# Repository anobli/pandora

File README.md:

# Pandora

Open Hardware and Open Source Home Automation Platform

## Overview

**Pandora** is an open platform for building robust home automation devices that gives users complete control over their smart home ecosystem. Built on the Zephyr RTOS and leveraging modern IoT protocols like WiFi and Thread/OpenThread with CoAP, Pandora addresses the key issues with current smart home devices: privacy concerns, cloud dependency, vendor lock-in, and planned obsolescence.

### Key Principles

- **User-repairable hardware** - Open hardware designs that users can modify and repair
- **Local processing** - No cloud dependency, all processing happens locally  
- **Open source software stack** - Complete control over firmware and functionality
- **Give back control to users** - No vendor lock-in or forced obsolescence

### Hermes Subsystem

The **Hermes subsystem** is the core IoT framework that provides:

- **Automatic Discovery**: Devices automatically discover and register with servers
- **State Management**: Comprehensive device lifecycle and state machine
- **CoAP Communication**: Both client and server functionality
- **Network Management**: Automatic connection and device provisioning
- **Persistent Settings**: Configuration survives device reboots
- **Extensible Architecture**: Easy to add new device types

## Current Status

### Working Features
- Power/Light switch devices running on Zephyr
- CoAP-based device discovery and control
- JSON API for device state management
- Multiple development platform support
- **WiFi connectivity**: ESP32/ESP32C6 with automatic provisioning
- **Thread networking**: CC1352P7 with OpenThread support
- Persistent configuration storage

### In Development
- MCUboot integration for secure OTA updates
- Enhanced security and encryption
- Matter protocol migration
- More device type support

## Quick Start

### Prerequisites
- Zephyr SDK and development environment
- Supported development board (ESP32 DevKit or CC1352P7-LP recommended)
- West tool for project management

### Building a Sample Application

```bash
# Clone the repository
git clone https://github.com/anobli/pandora.git
cd pandora

# Initialize west workspace
west init -l .
west update

# Build for WiFi-based device (ESP32)
west build -b esp32_devkitc_procpu samples/hermes/hermes_light

# Or build for Thread-based device (CC1352P7)
west build -b cc1352p7_lp samples/hermes/hermes_light

# Flash to device
west flash
```

## Device Types

### Currently Supported
- **Light Controllers**: On/off, dimming, color temperature, RGB control
- **Power Switches**: Relay-based switching modules

### Planned
- Light bulbs with integrated controllers
- Door/window sensors
- Motion detectors
- Climate sensors

## Integration

### CoAP2MQTT Bridge
For integration with MQTT-based home automation systems, use the companion [CoAP2MQTT](https://github.com/anobli/coap2mqtt) bridge.

#### Home Assistant Integration
Pandora devices integrate with Home Assistant through the CoAP2MQTT bridge:
- **CoAP to MQTT translation**: Bridge handles protocol conversion
- **Automatic device discovery** in Home Assistant via MQTT discovery
- **Standard entity types** (lights, switches, sensors)
- **Real-time state updates** with immediate response
- **Network flexibility**: Works with both WiFi and Thread networks

## Development

### Adding New Device Types

1. Create device tree bindings in `dts/bindings/`
2. Implement driver in `drivers/` if needed
3. Add device-specific service in `subsys/hermes/`
4. Create sample application in `samples/`

### Contributing

Contributions are welcome! Please see:
- **Hardware designs**: https://github.com/anobli/pandora-hw
- **CoAP2MQTT bridge**: https://github.com/anobli/coap2mqtt
- **Main firmware**: This repository

## License

This project is licensed under the Apache 2.0 License - see the individual file headers for details.

## Future Plans

- **Matter Support**: Migration from custom CoAP to Matter protocol
- **Enhanced Security**: Full encryption and secure provisioning
- **Consumer Products**: Moving beyond maker-friendly to consumer-ready devices
- **Extended Device Support**: More sensors, actuators, and device types
- **Cloud Integration**: Optional cloud services while maintaining local control

---

*Pandora: Giving users back control of their smart homes*

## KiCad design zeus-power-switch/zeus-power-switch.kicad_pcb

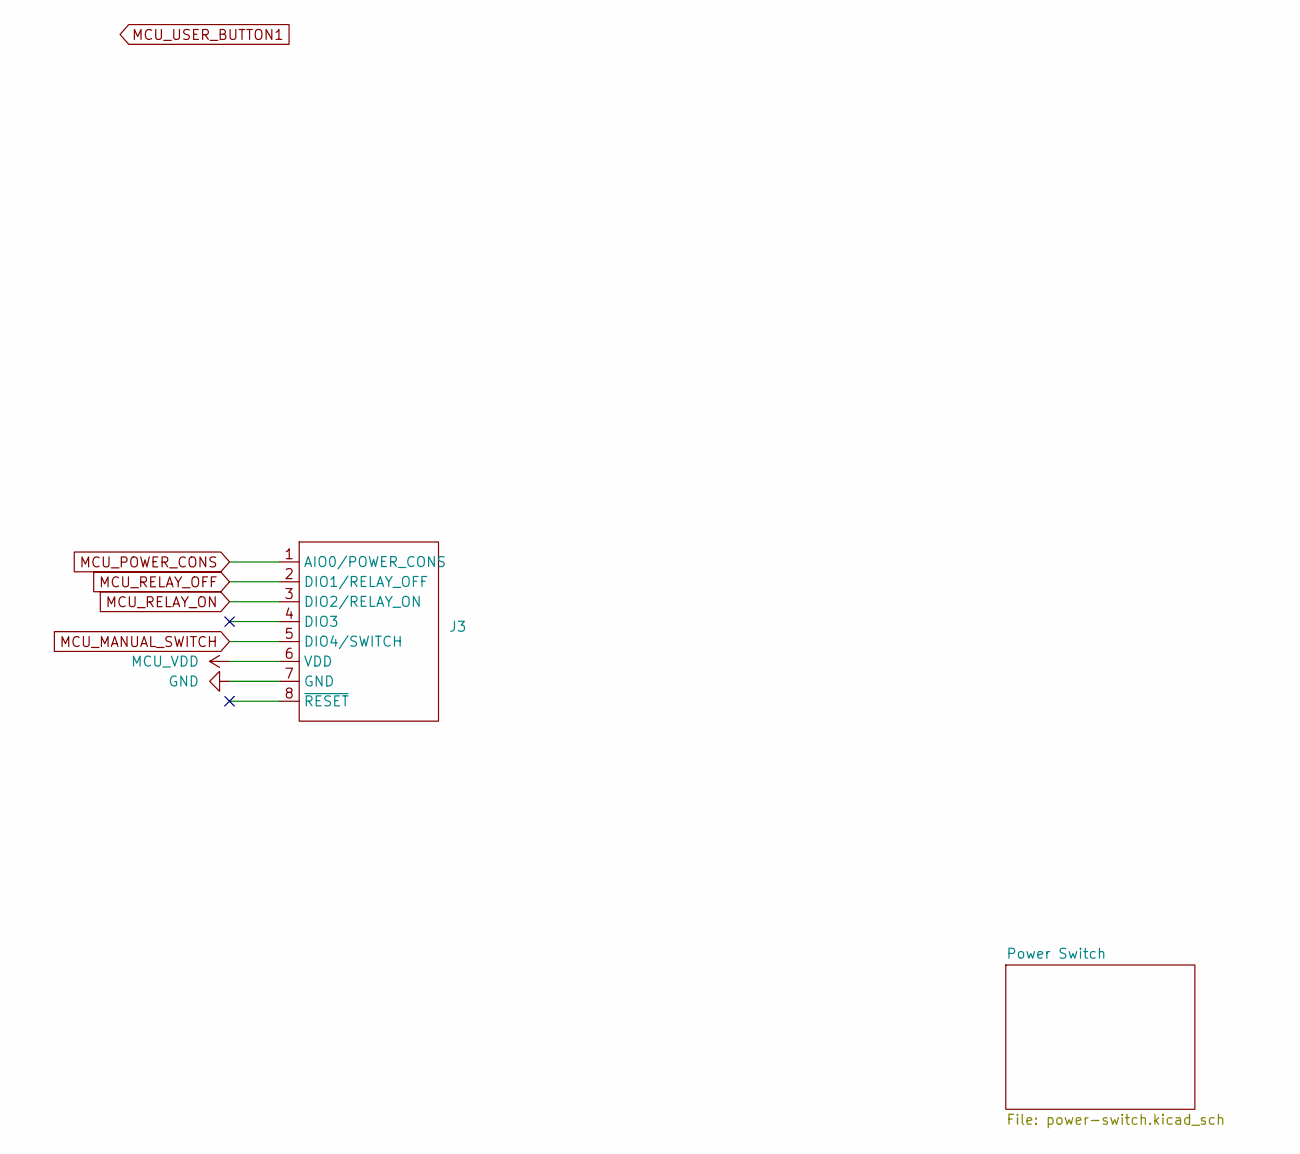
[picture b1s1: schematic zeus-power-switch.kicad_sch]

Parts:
J3: Zeus Connector_1

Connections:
GND: J3.7 (GND); also elsewhere on the board
MCU_MANUAL_SWITCH: J3.5 (DIO4/SWITCH); also elsewhere on the board
MCU_POWER_CONS: J3.1 (AIO0/POWER_CONS); also elsewhere on the board
MCU_RELAY_OFF: J3.2 (DIO1/RELAY_OFF); also elsewhere on the board
MCU_RELAY_ON: J3.3 (DIO2/RELAY_ON); also elsewhere on the board
MCU_VDD: J3.6 (VDD); also elsewhere on the board

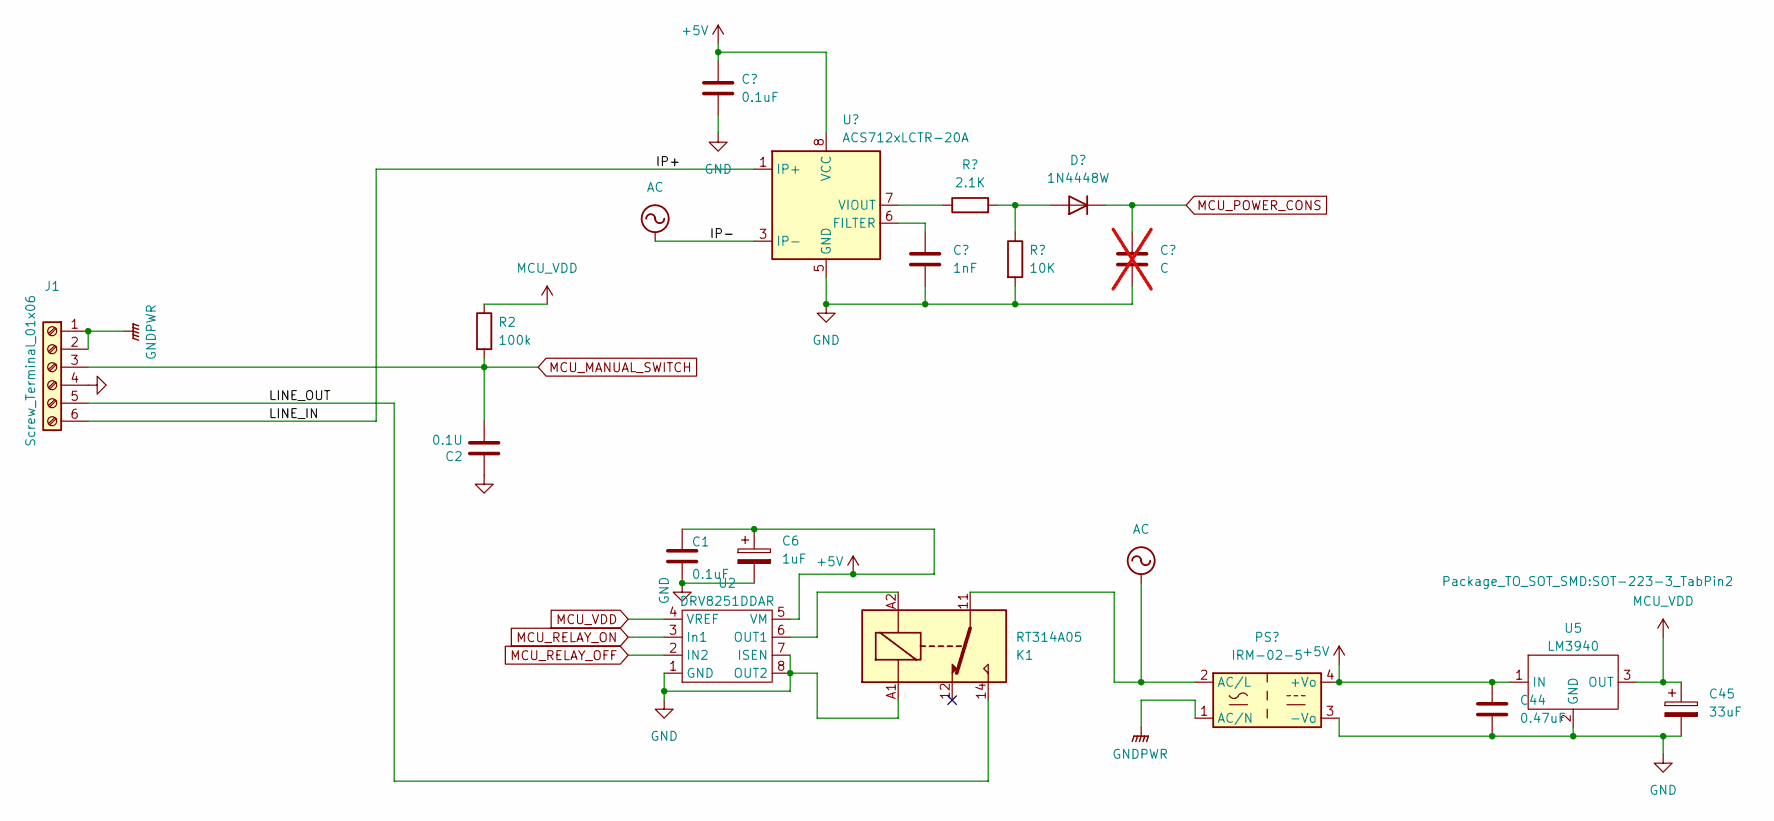
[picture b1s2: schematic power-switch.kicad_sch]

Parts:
C1, C3: 0.1uF; C_0402_1005Metric; MPN1 GRM155C81E104MA12D
C2: 0.1U; C_0402_1005Metric; MPN1 CL05A104MP5NNNC
C4: 1nF; C_0402_1005Metric; MPN1 VJ0402Y102MXBAC
C5: C; C_0402_1005Metric; not fitted
C6: 1uF; C_0402_1005Metric; MPN1 GRT153R61A105ME13D
C44: 0.47uF; C_0402_1005Metric; MPN1 GRM155R71A474KE01D
C45: 33uF; C_1206_3216Metric; MPN1 C3216X5R1E336M160AC
D3: 1N4448W; D_SOD-123; MPN1 1N4448W-7-F
J1: Screw_Terminal_01x06; TE-2-796683-8; MPN1 796683-6
K1: RT314A05; Relay_SPDT_Schrack-RT1-16A-FormC_RM5mm; MPN1 RT314A05
PS1: IRM-02-5; Converter_ACDC_MeanWell_IRM-02-xx_THT; MPN1 IRM-02-5
R2: 100k; R_0402_1005Metric; MPN1 CRCW0402100KFKED
R5: 2.1K; R_0402_1005Metric; MPN1 CRCW04022K10FKED
R7: 10K; R_0402_1005Metric; MPN1 CRCW040210K0FKEDC
U1: ACS712xLCTR-20A; SOIC-8_3.9x4.9mm_P1.27mm; MPN1 ACS712ELCTR-20A-T
U2: DRV8251DDAR; Texas_HSOP-8-1EP_3.9x4.9mm_P1.27mm_ThermalVias; MPN1 DRV8251DDAR
U5: LM3940; SOT-223-3_TabPin2; MPN1 LM3940IMP-3.3/NOPB

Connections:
+5V: C1.1, C3.1, C6.1, C44.1, PS1.4 (+Vo), U1.8 (VCC), U2.5 (VM), U5.1 (IN)
/Power Switch/IP+: J1.6, U1.1 (IP+), U1.2 (IP+)
/Power Switch/LINE_OUT: J1.5, K1.14
AC: K1.11, PS1.2 (AC/L), U1.3 (IP-), U1.4 (IP-)
GND: C1.2, C2.2, C3.2, C4.2, C5.2, C6.2, C44.2, C45.2, J1.4, K1.A1, PS1.3 (-Vo), R7.2, U1.5 (GND), U2.1 (GND), U2.7 (ISEN), U2.8 (OUT2), U5.2 (GND); also elsewhere on the board
GNDPWR: J1.1, J1.2, PS1.1 (AC/N)
MCU_MANUAL_SWITCH: C2.1, J1.3, R2.2; also elsewhere on the board
MCU_POWER_CONS: C5.1, D3.1 (K); also elsewhere on the board
MCU_RELAY_OFF: U2.2 (IN2); also elsewhere on the board
MCU_RELAY_ON: U2.3 (In1); also elsewhere on the board
MCU_VDD: C45.1, R2.1, U2.4 (VREF), U5.3 (OUT); also elsewhere on the board
unnamed: D3.2 (A), R5.2, R7.1
unnamed: C4.1, U1.6 (FILTER)
unnamed: R5.1, U1.7 (VIOUT)
unnamed: K1.A2, U2.6 (OUT1)

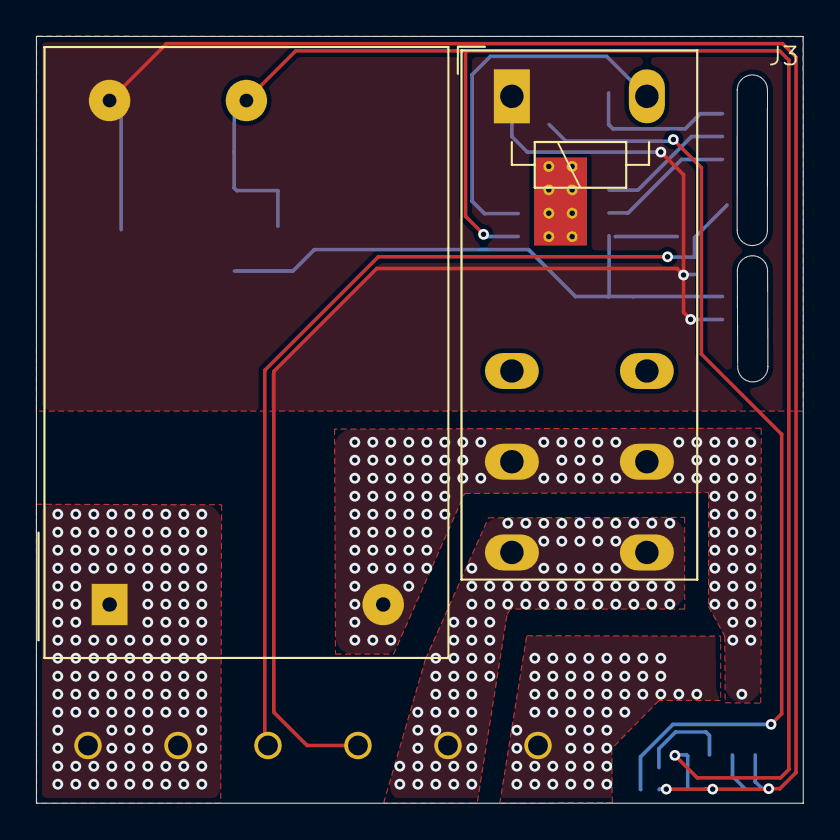
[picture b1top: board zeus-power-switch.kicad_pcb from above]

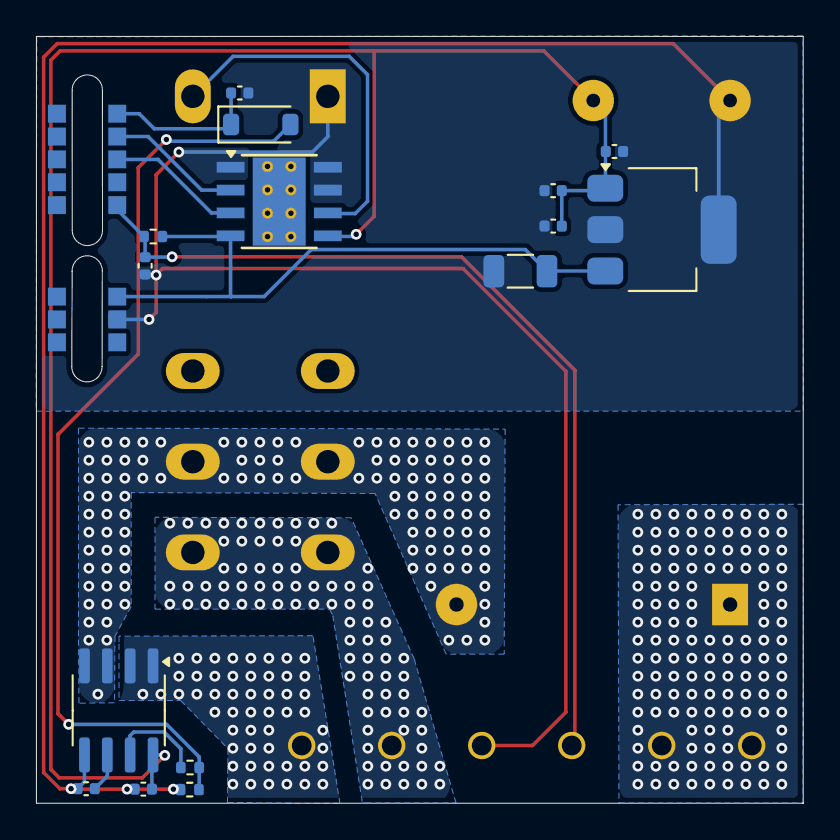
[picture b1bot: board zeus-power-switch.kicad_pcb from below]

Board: 2 copper layers, 42.6 x 42.6 mm, 19 parts (15 on the bottom side), 15 nets.

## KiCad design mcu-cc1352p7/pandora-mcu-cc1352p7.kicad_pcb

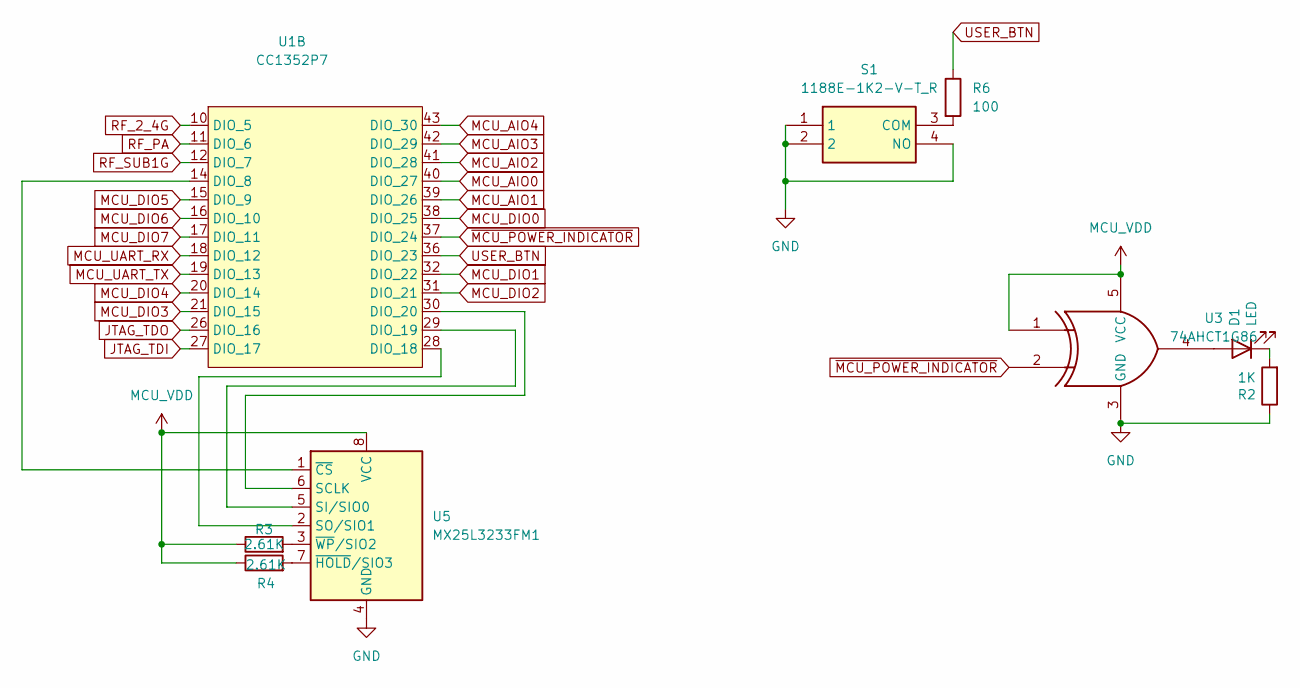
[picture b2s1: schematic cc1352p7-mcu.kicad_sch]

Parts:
D1: LED; LED_0402_1005Metric; MPN1 LT QH9G-Q2OO-25-2Z4Y-5-R18
R2: 1K; R_0402_1005Metric; MPN1 RC0402JR-071KL
R3, R4: 2.61K; R_0201_0603Metric
R6: 100; R_0402_1005Metric
S1: 1188E-1K2-V-T_R; 1188E1K2VTR; Mouser Part Number 113-1188E1K2VTR
U1: CC1352P7; Texas_RGZ0048A_VQFN-48-1EP_7x7mm_P0.5mm_EP5.15x5.15mm_Therm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; MPN1 CC1352P74T0RGZR
U3: 74AHCT1G86; SOT-23-5; MPN1 SN74AHCT1G86DBVT
U5: MX25L3233FM1; SOP-8_3.9x4.9mm_P1.27mm; MPN1 MX25L3233FM1I-08G

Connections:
GND: R2.1, S1.1, S1.2, S1.4 (NO), U3.3 (GND), U5.4 (GND); also elsewhere on the board
JTAG_TDI: U1.27 (DIO_17); also elsewhere on the board
JTAG_TDO: U1.26 (DIO_16); also elsewhere on the board
MCU_AIO0: U1.40 (DIO_27); also elsewhere on the board
MCU_AIO1: U1.39 (DIO_26); also elsewhere on the board
MCU_AIO2: U1.41 (DIO_28); also elsewhere on the board
MCU_AIO3: U1.42 (DIO_29); also elsewhere on the board
MCU_AIO4: U1.43 (DIO_30); also elsewhere on the board
MCU_DIO0: U1.38 (DIO_25); also elsewhere on the board
MCU_DIO1: U1.32 (DIO_22); also elsewhere on the board
MCU_DIO2: U1.31 (DIO_21); also elsewhere on the board
MCU_DIO3: U1.21 (DIO_15); also elsewhere on the board
MCU_DIO4: U1.20 (DIO_14); also elsewhere on the board
MCU_DIO5: U1.15 (DIO_9); also elsewhere on the board
MCU_DIO6: U1.16 (DIO_10); also elsewhere on the board
MCU_DIO7: U1.17 (DIO_11); also elsewhere on the board
MCU_UART_RX: U1.18 (DIO_12); also elsewhere on the board
MCU_UART_TX: U1.19 (DIO_13); also elsewhere on the board
MCU_VDD: R3.1, R4.1, U3.1, U3.5 (VCC), U5.8 (VCC); also elsewhere on the board
unnamed: D1.2 (A), U3.4
unnamed: D1.1 (K), R2.2
unnamed: R6.2, S1.3 (COM)
unnamed: U1.14 (DIO_8), U5.1 (~CS)
unnamed: U1.28 (DIO_18), U5.2 (SO/SIO1)
unnamed: U1.29 (DIO_19), U5.5 (SI/SIO0)
unnamed: U1.30 (DIO_20), U5.6 (SCLK)
unnamed: R4.2, U5.7 (~HOLD/SIO3)
unnamed: R3.2, U5.3 (~WP/SIO2)
RF_2_4G: U1.10 (DIO_5); also elsewhere on the board
RF_PA: U1.11 (DIO_6); also elsewhere on the board
RF_SUB1G: U1.12 (DIO_7); also elsewhere on the board
USER_BTN: R6.1, U1.36 (DIO_23)
~MCU_POWER_INDICATOR: U1.37 (DIO_24), U3.2

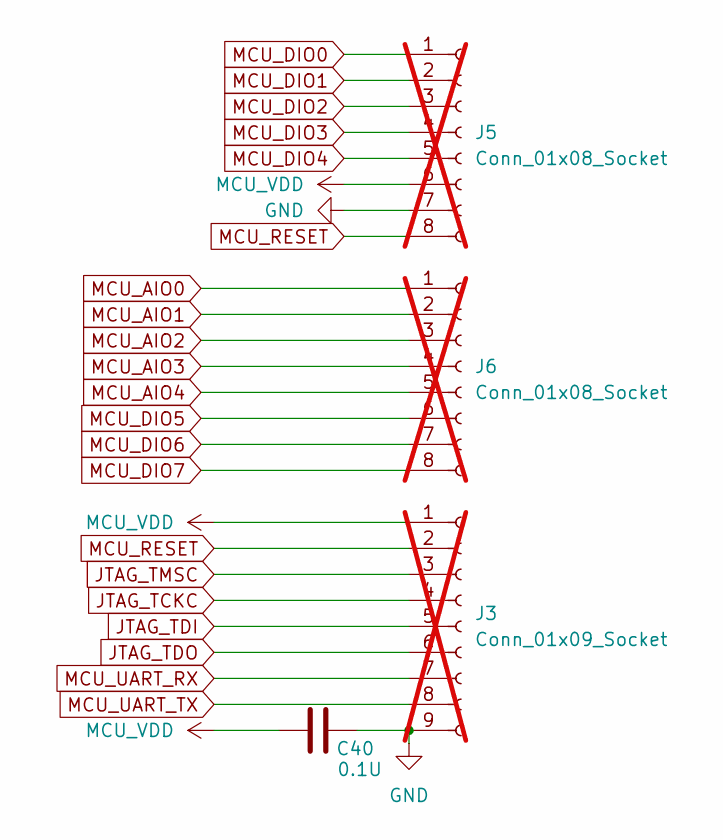
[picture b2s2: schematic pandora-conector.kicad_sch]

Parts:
C40: 0.1U; C_0402_1005Metric; MPN1 CL05A104MP5NNNC
J3: Conn_01x09_Socket; Pandora Connector 9; not fitted
J5: Conn_01x08_Socket; Zeus Connector; not fitted
J6: Conn_01x08_Socket; Pandora Connector 8; not fitted

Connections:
GND: C40.2, J3.9, J5.7; also elsewhere on the board
JTAG_TCKC: J3.4; also elsewhere on the board
JTAG_TDI: J3.5; also elsewhere on the board
JTAG_TDO: J3.6; also elsewhere on the board
JTAG_TMSC: J3.3; also elsewhere on the board
MCU_AIO0: J6.1; also elsewhere on the board
MCU_AIO1: J6.2; also elsewhere on the board
MCU_AIO2: J6.3; also elsewhere on the board
MCU_AIO3: J6.4; also elsewhere on the board
MCU_AIO4: J6.5; also elsewhere on the board
MCU_DIO0: J5.1; also elsewhere on the board
MCU_DIO1: J5.2; also elsewhere on the board
MCU_DIO2: J5.3; also elsewhere on the board
MCU_DIO3: J5.4; also elsewhere on the board
MCU_DIO4: J5.5; also elsewhere on the board
MCU_DIO5: J6.6; also elsewhere on the board
MCU_DIO6: J6.7; also elsewhere on the board
MCU_DIO7: J6.8; also elsewhere on the board
MCU_RESET: J3.2, J5.8; also elsewhere on the board
MCU_UART_RX: J3.7; also elsewhere on the board
MCU_UART_TX: J3.8; also elsewhere on the board
MCU_VDD: C40.1, J3.1, J5.6; also elsewhere on the board

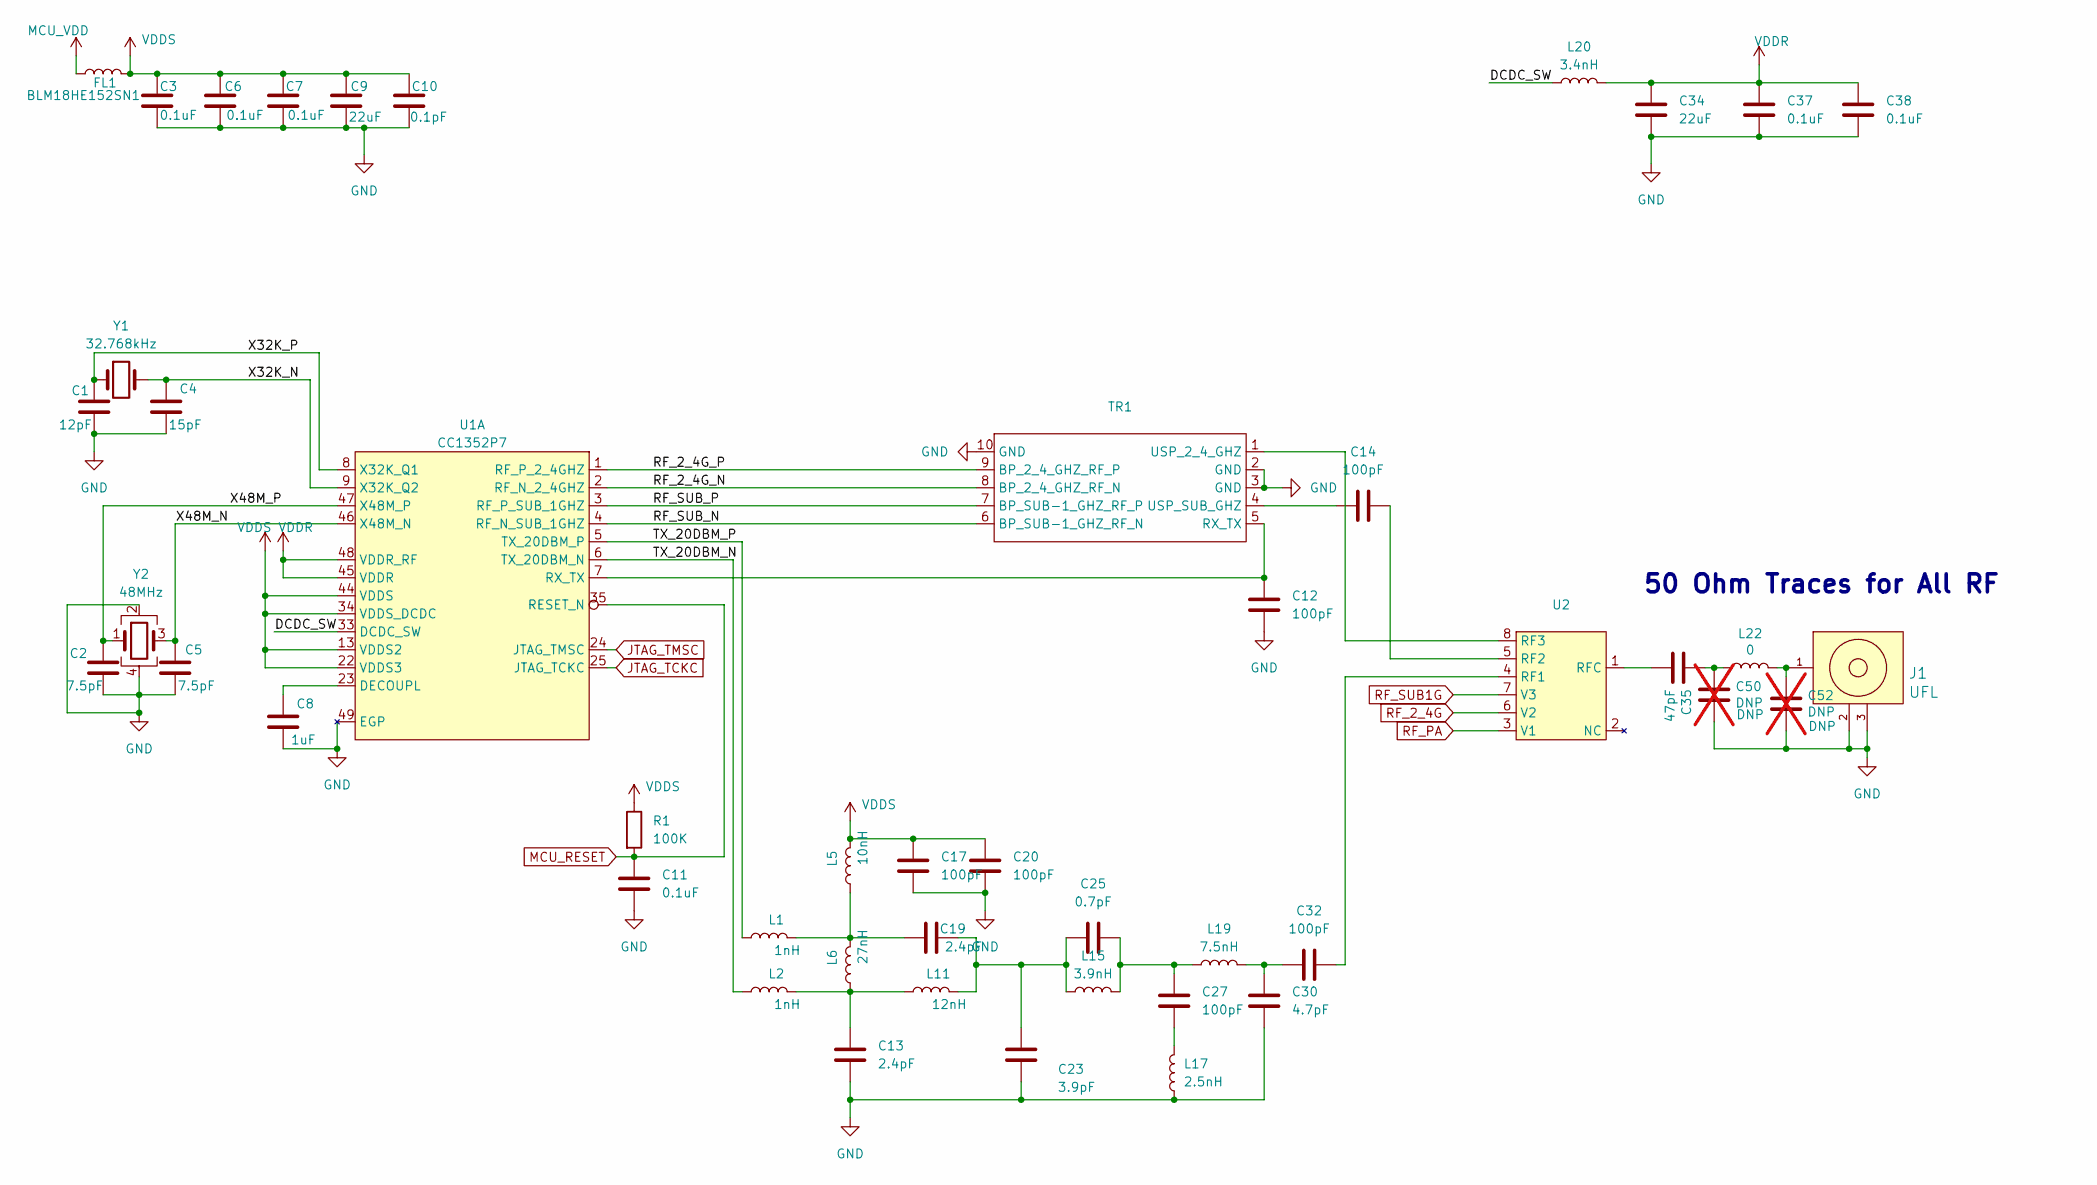
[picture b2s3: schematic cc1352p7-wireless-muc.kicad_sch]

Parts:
C1: 12pF; C_0201_0603Metric; MPN1 GJM1555C1H120JB01D
C2, C5: 7.5pF; C_0201_0603Metric; MPN1 GRM0335C1H7R5BA01J
C3, C6, C7, C11, C37, C38: 0.1uF; C_0402_1005Metric; MPN1 GRM155R71E104KE14D
C4: 15pF; C_0201_0603Metric; MPN1 GRT1555C1H150JA02D
C8: 1uF; C_0402_1005Metric; MPN1 GRM155C81C105KE15D
C9, C34: 22uF; C_0603_1608Metric; MPN1 GRM188R60J226MEA0D
C10: 0.1pF; C_0201_0603Metric; MPN1 GRM155R71E104KE14D
C12, C14: 100pF; C_0201_0603Metric
C13, C19: 2.4pF; C_0201_0603Metric; MPN1 GRM0335C1H2R4BA01J
C17, C20, C27, C32: 100pF; C_0201_0603Metric; MPN1 GRM0335C1H101GA01D
C23: 3.9pF; C_0201_0603Metric; MPN1 GRM0335C1H3R9BA01J
C25: 0.7pF; C_0201_0603Metric; MPN1 GRM0335C1HR70WA01D
C30: 4.7pF; C_0201_0603Metric; MPN1 GRM0335C1H4R7BA01J
C35: 47pF; C_0201_0603Metric; MPN1 GRM0335C1E470JA01D
C50: DNP; C_0201_0603Metric; MPN1 CC0402CRNPO9BN2R7; not fitted
C52: DNP; C_0201_0603Metric; MPN1 CC0402DRNPO9BN5R6; not fitted
FL1: BLM18HE152SN1; L_0603_1608Metric
J1: UFL; A-1JB; MPN1 A-1JB
L1, L2: 1nH; L_0201_0603Metric; MPN1 LQP03TN3N7B02J
L5: 10nH; L_0201_0603Metric; MPN1 LQP03TN12NHZ2J
L6: 27nH; L_0201_0603Metric; MPN1 LQP03TN27NHZ2J
L11: 12nH; L_0201_0603Metric; MPN1 LQP03TN12NHZ2J
L15: 3.9nH; L_0201_0603Metric; MPN1 LQP03TN3N9B02J
L17: 2.5nH; L_0201_0603Metric; MPN1 LQP03TN2N5B02J
L19: 7.5nH; L_0201_0603Metric; MPN1 LQP03TN7N5HZ2J
L20: 3.4nH; L_0201_0603Metric; MPN1 LQP03TN3N4B02J
L22: 0; L_0201_0603Metric; MPN1 RMCF0402ZT0R00
R1: 100K; R_0402_1005Metric; MPN1 CRCW0402100KJNED
TR1: IPC1352; MPN1 LFB21868MDZ5E757
U1: CC1352P7; Texas_RGZ0048A_VQFN-48-1EP_7x7mm_P0.5mm_EP5.15x5.15mm_Therm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; MPN1 CC1352P74T0RGZR
U2: Skyworks_SKY1337-373LF; MPN1 SKY13317-373LF
Y1: 32.768kHz; Crystal_SMD_2012-2Pin_2.0x1.2mm; MPN1 830050789
Y2: 48MHz; Crystal_SMD_2016-4Pin_2.0x1.6mm; MPN1 ASDAIG-48.000MHZ-X-K-T

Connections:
/CC1352P7-Wireless-MCU/DCDC_SW: L20.1, U1.33 (DCDC_SW)
/CC1352P7-Wireless-MCU/RF_2_4G_N: TR1.8 (BP_2_4_GHZ_RF_N), U1.2 (RF_N_2_4GHZ)
/CC1352P7-Wireless-MCU/RF_2_4G_P: TR1.9 (BP_2_4_GHZ_RF_P), U1.1 (RF_P_2_4GHZ)
/CC1352P7-Wireless-MCU/RF_SUB_N: TR1.6 (BP_SUB-1_GHZ_RF_N), U1.4 (RF_N_SUB_1GHZ)
/CC1352P7-Wireless-MCU/RF_SUB_P: TR1.7 (BP_SUB-1_GHZ_RF_P), U1.3 (RF_P_SUB_1GHZ)
/CC1352P7-Wireless-MCU/TX_20DBM_N: L2.1, U1.6 (TX_20DBM_N)
/CC1352P7-Wireless-MCU/TX_20DBM_P: L1.1, U1.5 (TX_20DBM_P)
/CC1352P7-Wireless-MCU/X32K_N: C4.1, U1.9 (X32K_Q2), Y1.2
/CC1352P7-Wireless-MCU/X32K_P: C1.1, U1.8 (X32K_Q1), Y1.1
/CC1352P7-Wireless-MCU/X48M_N: C5.1, U1.46 (X48M_N), Y2.3
/CC1352P7-Wireless-MCU/X48M_P: C2.1, U1.47 (X48M_P), Y2.1
GND: C1.2, C2.2, C3.2, C4.2, C5.2, C6.2, C7.2, C8.2, C9.2, C10.2, C11.2, C12.1, C13.1, C17.1, C20.1, C23.1, C30.1, C34.2, C37.2, C38.2, C50.2, C52.2, J1.2, J1.3, L17.1, TR1.2 (GND), TR1.3 (GND), TR1.10 (GND), U1.49 (EGP), Y2.2, Y2.4; also elsewhere on the board
JTAG_TCKC: U1.25 (JTAG_TCKC); also elsewhere on the board
JTAG_TMSC: U1.24 (JTAG_TMSC); also elsewhere on the board
MCU_RESET: C11.1, R1.2, U1.35 (RESET_N); also elsewhere on the board
MCU_VDD: FL1.1; also elsewhere on the board
unnamed: C13.2, L2.2, L6.1, L11.1
unnamed: C19.1, L1.2, L5.1, L6.2
unnamed: C19.2, C23.2, C25.2, L11.2, L15.1
unnamed: C25.1, C27.2, L15.2, L19.1
unnamed: C27.1, L17.2
unnamed: C30.2, C32.1, L19.2
unnamed: C35.2, C50.1, L22.2
unnamed: C52.1, J1.1, L22.1
unnamed: C12.2, TR1.5 (RX_TX), U1.7 (RX_TX)
unnamed: TR1.1 (USP_2_4_GHZ), U2.8 (RF3)
unnamed: C14.1, TR1.4 (USP_SUB_GHZ)
unnamed: C8.1, U1.23 (DECOUPL)
unnamed: C32.2, U2.4 (RF1)
unnamed: C14.2, U2.5 (RF2)
unnamed: C35.1, U2.1 (RFC)
RF_2_4G: U2.6 (V2); also elsewhere on the board
RF_PA: U2.3 (V1); also elsewhere on the board
RF_SUB1G: U2.7 (V3); also elsewhere on the board
VDDR: C34.1, C37.1, C38.1, L20.2, U1.45 (VDDR), U1.48 (VDDR_RF)
VDDS: C3.1, C6.1, C7.1, C9.1, C10.1, C17.2, C20.2, FL1.2, L5.2, R1.1, U1.13 (VDDS2), U1.22 (VDDS3), U1.34 (VDDS_DCDC), U1.44 (VDDS)

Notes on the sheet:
50 Ohm Traces for All RF

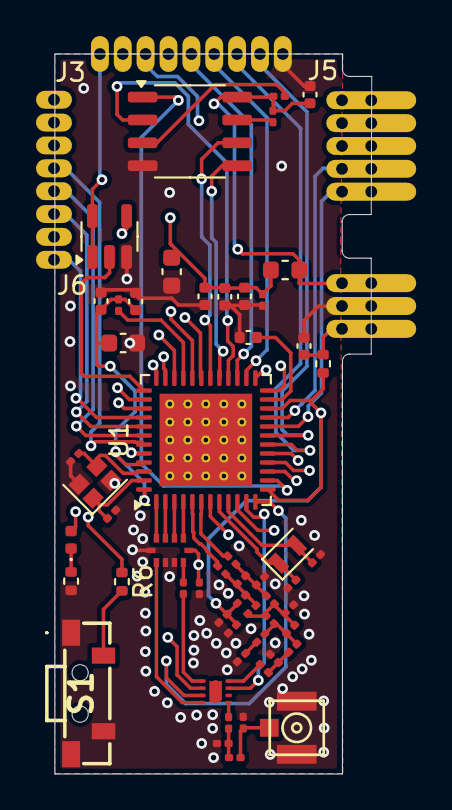
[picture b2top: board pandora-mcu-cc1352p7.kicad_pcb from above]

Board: 4 copper layers, 17.6 x 40.0 mm, 58 parts (0 on the bottom side), 64 nets.

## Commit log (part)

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2025-02-25 Create Pandora project
    Pandora projects intends to develop open source and open hardware
    solutions for the home automation.
    This adds the kicad projects for Zeus board (a connected power switch)
    and the MCU board. This is the DVT0 version.
2025-06-11 Initial commit
    Create a new tree for Pandora project.
    Pandora intends to provides open sources firmware for home automation
    devices. It first intends to support open hardware devices but it will
    also support ESP32 based devices.
    This will provides BSP, samples for demonstrating some connectivity
    features and full applications.
2025-06-13 Add .clang-format from Zephyr
    In order to use clang-format, add .clang-format.
    Because most of the code here is intended to be upstreamed to Zephyr,
    use the same config.
2025-06-13 drivers: sensor: Add support of sensor simulator
    This adds a simulator for sensor.
    This could be used for unit tests or for development when
    using the sensor API with native sim.
2025-06-13 samples: Add a sample demonstrating how using the sensor simulator
    This adds a basic example show how to use the sensor simulator.
    This shows how we could set default value and noise programmatically.
    An alternative way of doing it is using DTS which allow using the
    simulator with regular sample applications using the sensor API.
2025-07-31 WIP: First working light sample
2025-07-31 add narada light sample
2025-07-31 WIP: Add a light sample using narada
2025-07-31 minor fix to narada
2025-08-04 add support of rgbct light
2025-08-23 pandora: Add support of syscall
    We are going to define new driver APIs.
    This adds anything required to do it.
2025-08-23 subsys: Add support of hermes
    This adds hermes, a library that implements communication
    between home automation devices.
2025-08-23 hermes: Add support of settings
    This adds support of settings.
    This allows saving and restoring entity state after a power cycle.
    We may also want to save some user settings later such as schedules
    if status LED should be enabled or not, and so on.
2025-08-23 Add a README
    This adds a README file to explain what is Pandora.
2025-08-23 hermes: Add a shell for hermes
    This adds a development shell for hermes.
    This is useful as example to reset device configuration.
2025-08-24 Add license file and update sources with SPDX license
    Currently, the license is not clearly defined.
    This makes sure that everything is clearly defined.
2025-08-26 drivers: light: Add support of light GPIO driver
    This adds support of a GPIO light driver.
2025-08-28 hermes: Add support of native_sim target
    This adds some changes required to use native_sim
    for developping and testing hermes.
2025-10-28 Add support of ESPHOME
    This add a preliminary support of ESPHOME to zephyr.
    This currently supports the following components:
    - api
    - hbridge and gpio switch
    - button
    - gpio binary sensor
2025-10-28 net: esphome: esphome: Fix the loop delay
    The on_loop method is expected to be run every 16ms.
    This updates the delay to respect it.
2025-10-28 esphome: switch: hbridge: Fix a build issue in the hbridge component
    This addresses a build issue in the hbridge switch component.
2025-10-28 net: esphome: logger: Add missing Kconfig symbol
    CMake is expecting a Kconfig symbol to build the logger
    but this symbols is never defined.
    This defines a kconfig symbol and use it in CMake.
2025-10-28 ESPHome app: Add a config overlay to enable support of OpenThread
    This adds an overlay to enable support of OpenThread network.
    The overlay use predefined newtork settings which allow testing
    quickly a device using OpenThread.
2025-10-28 app: Add zeus board to sample.yaml
    This will be used to make sure zeus is building correctly.
2025-10-28 CI: Add codecheck config files
    In order to run some static analysis tools, add config files
    for CodeChecker which is going to be run from CI.
2025-10-28 bindings: Update DT bindings using west esphome command
    This updates the bindings using the new esphome dts_bindings command.
    This makes sure that the bindings are always aligned on what could be
    generated using the yaml files.
2025-10-28 app: Add support of Zeus to esphome test application
    This adds support of Zeus to esphome test application.
    This is probably not complete but it should be enough for testing it.
2025-10-28 app: Add a sample.yaml
    This is going to be used by twister to make sure the application
    build for supported and tested platforms.
2025-10-28 Test: Add a folder to host CodeChecker report
2025-12-08 ESPHome: Simplify bindings
    This improves a little the switch bindings.
    WE have some properties that are common to almost all
    ESPHome components. This updates the bindings to include
    the common binding that defines them.
2025-12-08 Add a specific logger to ESPHome OpenThread integration
    In order to filter logs specific to OpenThread integration,
    use a dedicated logger.
2025-12-08 ESPHome: OpenThread: SRP: Add TXT records
    ESPHome integration in HomeAssistant relies on TXT records
    to discover automatically a ESPHome device.
    This adds the expected TXT records and allow HomeAssistant
    to discover the device automatically.
2025-12-08 ESPHome: app: Update BeagleConnect Freedom DTS
    This removes the password which is now optionnal
    and set some name strings with a better value.
2025-12-08 Hermes: Move the library in subsys/net/lib
    In order to have some coherency, move hermes to same folder as
    esphome. This should also make easier code between the two
    protocols.
2025-12-09 Hermes: Move out some hermes API to Pandora
    In order to leverage maintainance and development
    move out some API from hermes to pandora.
    This will make this API and services available to ESPHome.
2025-12-18 app: beagleconnect_freedom: Enable support of factory reset
    This enables factory reset dependencies.
    This allows doing a factory reset by pressing boot button
    for 2 seconds.
2025-12-18 app: openthread overlay: Use joiner autostart
    Instead of configuring network using configuration,
    enable the joiner on start. If the device is not
    commissioned then it starts the joiner to find
    and join an existing network.
2025-12-18 esphome: app: beagleconnect_freedom: Enable OTA support
    This enables support of ESPHome OTA.
    By using ESPHome python library, we could deploy and update
    a new firmware to a device connected on Thread network.
2025-12-18 esphome: Update OTA to work with OpenThread
    Currently, we wait until we got all the requested data from client.
    This works well with wifi but not with OpenThread which hangs
    because it doesn't receive enough data (due to memory limitation).
    Update the OTA component to deal with packet smaller than requested.
2025-12-18 subsys: pandora: Add support of factory reset
    This adds a component to perform a factory reset.
    This waits for an input and when this input match then
    it erases all the differents settings set by all the
    different components.
2025-12-18 pandora: service: Update to use latest SMF API
    SMF has been updated in latest Zephyr.
    This updates Pandora service to use latest API.
2025-12-19 drivers: gpio: Create a GPIO fake driver
    To test the switch hbridge component, we have to validate the state of two gpios
    and their state for a pperiod of time.
    This adds a GPIO fake driver which allows getting a history call of functions
    with the argument values.
2025-12-19 esphome: ota: make possible to build OTA without ESPHome
    ESPHome OTA protocol has its own stack fully independent
    of ESPHome itself. This updates cmake to make possible building it
    without ESPHome.
2026-01-05 esphome: ota: Add timeout for recv operations
    Most operations use ZSOCK_MSG_WAITALL.
    This simplify a lot the code but by default it waits
    indefinitely which make OTA hangs in case of network error
    (I noticed some with when using Thread).
    This adds a timeout so we could detect when something is going
    wrong and reset OTA.
2026-01-05 ESPHome: OTA: Add more logs to make easier to debug OTA
    In case of error, it is difficult to figure out what happened.
    This adds more logs, and also increase some logs level.
2026-01-05 ESPHome: OTA: Address issues found by tests
    While developing and running tests, I found some issues.
    To address them, send more error code to OTA client.
    This also removes unused function that was causing warning.
2026-01-06 esphome: ota: Add missing dependency
    ESPhome OTA can't build without CONFIG_REBOOT.
    This updates Kconfig to add this dependency.
2026-01-06 tests: esphome: ota: Add a test for MD5
    The client send to server the md5 hash to OTA server.
    This makes sure that OTA server use it to validate data integrity.
2026-01-19 ESPHome: Update entity to use DT node instead of inst
    We want to use the same components for ESPHome and Hermes.
    In order to achieve, we need to rework some code such as entity.
    This updates entity to use DT node instead of DT inst.
    This would allow using DT entity macro without defining DT_DRV_COMPAT.
    The goal is to use the generic component and just data required
    by ESPHome from component node.
2026-01-23 Address formating issue
    Address formating issue find by clang-format.
2026-01-23 pandora: component: Add an iterable section for components
    This adds an interable section for components.
    This allows listing and filtering pandora components by type.
2026-01-23 tests: pandora: pipeline: This adds tests for pipeline component
    This adds tests to validate the pipeline component.
2026-01-23 esphome: switch: Update esphome switch component to use pandara's one
    This updates ESPHome to use the generic switch component.
    This also removes the esphome one.
2026-01-23 pandora: switch: gpio: Fix a bug in gpio switch driver
    The initial state set in the driver is -EINVAL which is
    not some same as GPIO state (set to inactive state).
    This sets internal driver to the same state.
2026-01-23 pandora: component: Add binary_sensor component
    This adds the binary_sensor component and a gpio driver for it.
    Currently, this only provides on_state callback.
    This is going to be completed later:
    - add other callback support (on_click, double_click, multi_click)
    - provide a way to register, configure and enable them using DT
2026-01-23 pandora: add a shell for pandora
    This adds a shell for pandora.
    This doesn't add any command, just the minimum required
    to a commands later.
2026-01-23 pandora: component: Create switch component
    This adds the switch component. This is based on the ESPHome switch component,
    and actually, this is going to replace it.
    The goal is to make the component usable by ESPHome or Hermes stacks.
2026-01-23 boards: zeus: Update board to support the SPI flash
    The external SPI flash was not supported.
    This updates the board to support it.
    This is mostly required for OTA but we may consider using later
    for storing sensor data.
2026-01-23 esphome: api: Add a way to get api device
    If we want to send unsolicited request to HomeAssistant,
    we need to get a pointer to api device.
    This provides a macro for doing it.
2026-01-23 esphome: implement SubscribeState
    The SubscribeStatesRequestCb function is required by
    HomeAssitant to get the enties state.
    This is preliminary support, to be improved.
2026-01-23 eshpome: switch: Add callback to publish state on update
    This adds a callback to notify HomeAssistant when the switch state change.
